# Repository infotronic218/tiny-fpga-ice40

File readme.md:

# Tiny FPGA BOARD DESIGN With KiCad6

# This a simple PFC projec with KiCad 6 based on Lattice ICE40 Serie FPGA 
## The design has 4 layers

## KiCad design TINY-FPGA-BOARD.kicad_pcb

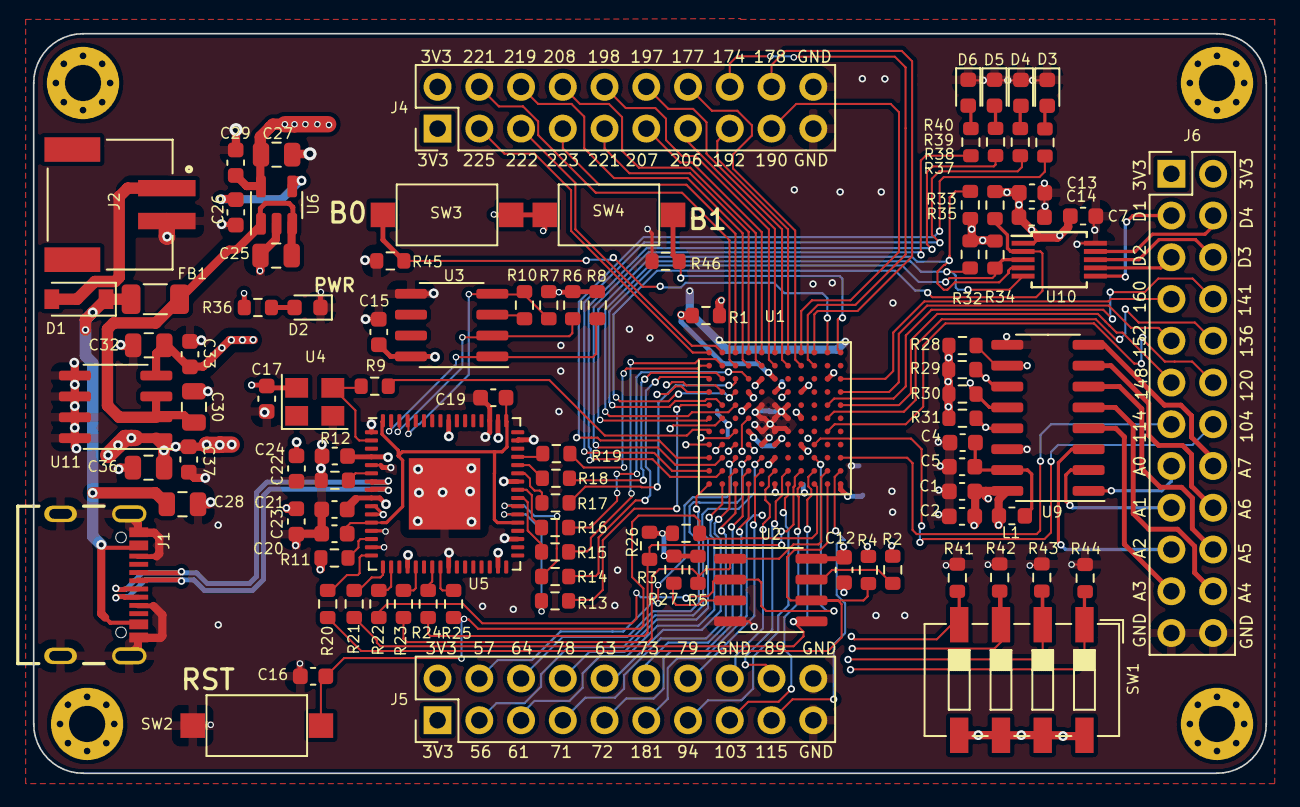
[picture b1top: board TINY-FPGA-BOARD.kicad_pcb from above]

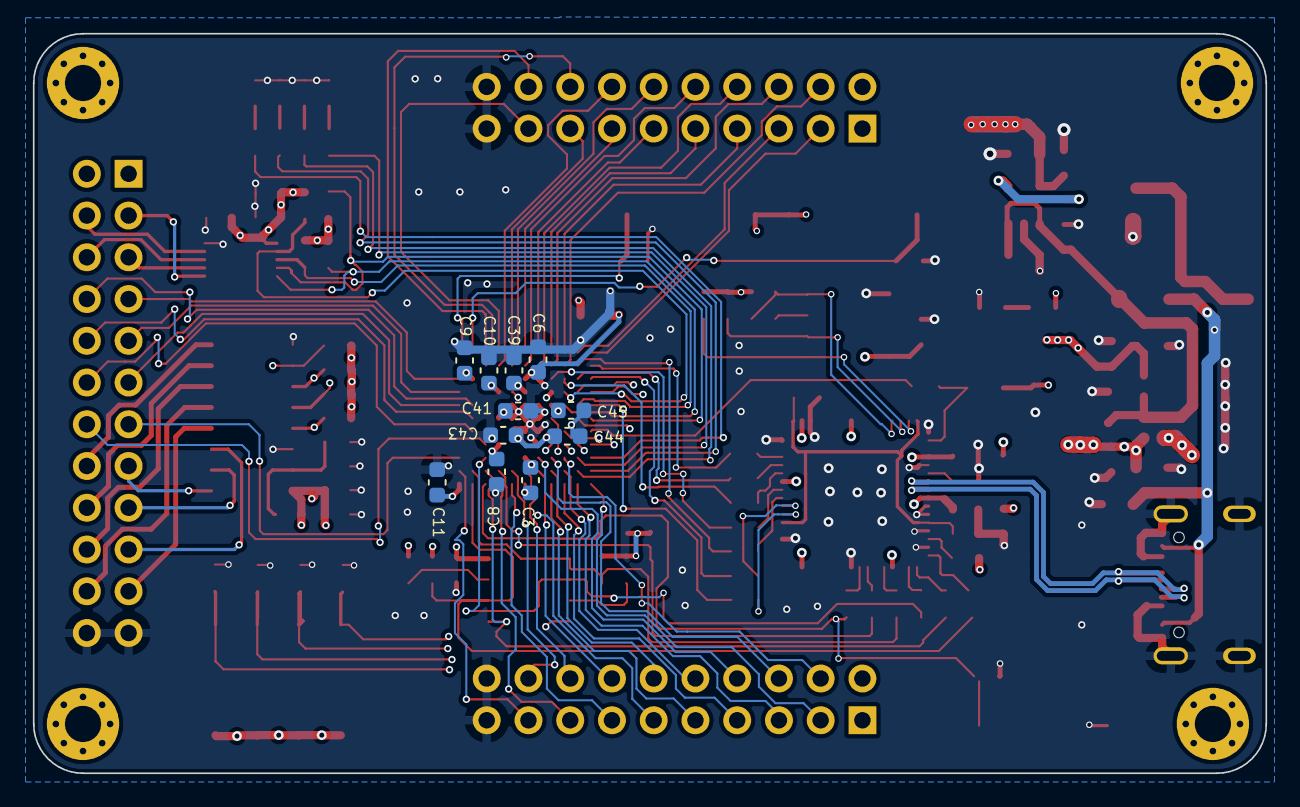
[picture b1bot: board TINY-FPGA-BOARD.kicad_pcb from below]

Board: 4 copper layers, 75.0 x 45.0 mm, 114 parts (11 on the bottom side), 124 nets.

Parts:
C1, C2, C4, C6, C7, C8, C9, C10, C11, C12, C13, C14, C15, C16, C17, C20, C23, C24, C26, C29, C33, C37, C39, C41, C43, C44, C45: 100n; C_0603_1608Metric
C3: 10u; C_0603_1608Metric
C5: 22pF; C_0603_1608Metric
C19, C21, C22: 4.7u; C_0603_1608Metric
C25, C27, C28, C30, C32, C36: 10u; C_0805_2012Metric
D1: D_Schottky; D_SOD-123
D2, D3, D4, D5, D6: LED; LED_0603_1608Metric
FB1: FerriteBead_Small; C_1206_3216Metric
H1, H2, H3, H4: MH; MountingHole_2.2mm_M2_Pad_Via
J1: CON_USB_GCT_USB4105_REVA
J2: DC; JST_S2B-PH-SM4-TB(LF)(SN)
J4, J5: CON; PinHeader_2x10_P2.54mm_Vertical
J6: Conn_02x12_Odd_Even; PinHeader_2x12_P2.54mm_Vertical
L1: 39nH; L_0603_1608Metric
R1: 100R; R_0603_1608Metric
R2, R3, R4, R5, R6, R7, R8, R26, R27, R28, R29, R30, R31, R32, R33, R34, R35, R41, R42, R43, R44, R45, R46: 10K; R_0603_1608Metric
R9, R13, R14, R15, R16, R17, R18, R19, R20, R21, R22, R23, R24, R25: 0R; R_0603_1608Metric
R10, R11: 2.2K; R_0603_1608Metric
R12: 12K; R_0603_1608Metric
R36, R37, R38, R39, R40: 220R; R_0603_1608Metric
SW1: SW_DIP_x04; SW_DIP_SPSTx04_Slide_6.7x11.72mm_W6.73mm_P2.54mm_LowProfile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
SW2, SW3, SW4: RST; SW_SPST_CK_RS282G05A3
U1: ICE40HX8K-BG121; BGA-121_9.0x9.0mm_Layout11x11_P0.8mm_Ball0.4mm_Pad0.35mm_NS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
U2: W25Q128JVS; SOIC-8_3.9x4.9mm_P1.27mm
U3: 93LCxxA; SOIC-8_3.9x4.9mm_P1.27mm
U4: ASDMB-xxxMHz; Crystal_SMD_Abracon_ABM8G-4Pin_3.2x2.5mm
U5: FT2232HQ; QFN-64-1EP_9x9mm_P0.5mm_EP4.35x4.35mm
U6: LDK130-12_SOT23_SOT353; SOT-23-5
U9: MCP3208; SOIC-16_3.9x9.9mm_P1.27mm
U10: MCP4728; MSOP-10_3x3mm_P0.5mm
U11: MIC5212-SJYM; SOIC-8_3.9x4.9mm_P1.27mm

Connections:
+1V2: C8.1, C10.1, C27.1, C29.1, R1.2, U1.D4 (VCC), U1.D8 (VCC), U1.H4 (VCC), U1.H8 (VCC), U6.5 (OUT)
+2V5: C9.1, C32.1, C33.1, U1.C10 (VPP_2V5), U11.4 (OUTB)
+3V3: C1.1, C2.1, C7.1, C11.1, C12.1, C13.1, C14.1, C15.2, C17.1, C21.1, C22.1, C23.1, C24.1, C36.2, C37.2, C39.1, C41.1, C43.1, C44.1, C45.1, J4.1, J4.2, J5.1, J5.2, J6.1, J6.2, L1.1, R2.2, R3.2, R4.2, R5.2, R6.2, R7.2, R8.2, R11.2, R26.2, R27.2, R28.2, R29.2, R30.2, R31.2, R32.2, R33.2, R34.2, R35.2, R36.2, SW1.5, SW1.6, SW1.7, SW1.8, SW3.1, SW4.1, U1.D6 (VCCIO_0), U1.E4 (VCCIO_3), U1.F8 (VCCIO_1), U1.G4 (VCCIO_3), U1.H6 (VCCIO_2), U1.L11 (VCC_SPI), U2.8 (VCC), U3.8 (VCC), U4.4 (VDD), U5.4 (VPHY), U5.9 (VPLL), U5.20 (VCCIO), U5.31 (VCCIO), U5.42 (VCCIO), U5.50 (VREGIN), U5.56 (VCCIO), U9.16 (Vdd), U10.1 (VDD), U11.1 (OUTA)
+5V: C25.1, C30.1, FB1.2, U6.1 (IN), U6.3 (EN), U11.2 (INA), U11.3 (INB)
/CS: R5.1, R23.1, U1.K10 (IOB_108_SS), U2.1 (~CS)
/FPGA IOs BANKS/BTN0: R45.2, SW3.2, U1.A10 (IOT_170)
/FPGA IOs BANKS/BTN1: R46.2, SW4.2, U1.A11 (IOT_168)
/FPGA IOs BANKS/IO56: J5.3, U1.L1 (IOB_56)
/FPGA IOs BANKS/IO57: J5.4, U1.J3 (IOB_57)
/FPGA IOs BANKS/IO61: J5.5, U1.L2 (IOB_61)
/FPGA IOs BANKS/IO63: J5.10, U1.K3 (IOB_63)
/FPGA IOs BANKS/IO64: J5.6, U1.J4 (IOB_64)
/FPGA IOs BANKS/IO71: J5.7, U1.L3 (IOB_71)
/FPGA IOs BANKS/IO72: J5.9, U1.L4 (IOB_72)
/FPGA IOs BANKS/IO73: J5.12, U1.K4 (IOB_73)
/FPGA IOs BANKS/IO78: J5.8, U1.J5 (IOB_78)
/FPGA IOs BANKS/IO79: J5.14, U1.K5 (IOB_79)
/FPGA IOs BANKS/IO82: J5.16, U1.K6 (IOB_82_GBIN4)
/FPGA IOs BANKS/IO89: J5.18, U1.K7 (IOB_89)
/FPGA IOs BANKS/IO94: J5.13, U1.L7 (IOB_94)
/FPGA IOs BANKS/IO103: J5.15, U1.L8 (IOB_103_CBSEL0)
/FPGA IOs BANKS/IO104: J6.14, U1.H9 (IOB_104_CBSEL1)
/FPGA IOs BANKS/IO114: J6.13, U1.J11 (IOR_114)
/FPGA IOs BANKS/IO115: J5.17, U1.K11 (IOR_115)
/FPGA IOs BANKS/IO120: J6.12, U1.G10 (IOR_120)
/FPGA IOs BANKS/IO136: J6.10, U1.F10 (IOR_136)
/FPGA IOs BANKS/IO141: J6.8, U1.E10 (IOR_141_GBIN2)
/FPGA IOs BANKS/IO148: J6.11, U1.E11 (IOR_148)
/FPGA IOs BANKS/IO152: J6.9, U1.D11 (IOR_152)
/FPGA IOs BANKS/IO160: J6.7, U1.C11 (IOR_160)
/FPGA IOs BANKS/IO174: J4.16, U1.B9 (IOT_174)
/FPGA IOs BANKS/IO177: J4.14, U1.B8 (IOT_177)
/FPGA IOs BANKS/IO178: J4.18, U1.A9 (IOT_178)
/FPGA IOs BANKS/IO181: J5.11, U1.D7 (IOT_181)
/FPGA IOs BANKS/IO190: J4.17, U1.A8 (IOT_190)
/FPGA IOs BANKS/IO192: J4.15, U1.A7 (IOT_192)
/FPGA IOs BANKS/IO197: J4.12, U1.B7 (IOT_197_GBIN1)
/FPGA IOs BANKS/IO198: J4.10, U1.B6 (IOT_198_GBIN0)
/FPGA IOs BANKS/IO206: J4.13, U1.A6 (IOT_206)
/FPGA IOs BANKS/IO207: J4.11, U1.A5 (IOT_207)
/FPGA IOs BANKS/IO208: J4.8, U1.B5 (IOT_208)
/FPGA IOs BANKS/IO211: J4.9, U1.A4 (IOT_211)
/FPGA IOs BANKS/IO219: J4.6, U1.B4 (IOT_219)
/FPGA IOs BANKS/IO221: J4.4, U1.B3 (IOT_221)
/FPGA IOs BANKS/IO222: J4.5, U1.A2 (IOT_222)
/FPGA IOs BANKS/IO223: J4.7, U1.A3 (IOT_223)
/FPGA IOs BANKS/IO225: J4.3, U1.A1 (IOT_225)
/FPGA IOs BANKS/LED1: R37.2, U1.J1 (IOL_23A)
/FPGA IOs BANKS/LED2: R38.2, U1.K1 (IOL_23B)
/FPGA IOs BANKS/LED3: R39.2, U1.K2 (IOL_25A)
/FPGA IOs BANKS/LED4: R40.2, U1.J2 (IOL_25B)
/FPGA IOs BANKS/SW1: R44.2, SW1.1, U1.D1 (IOL_8B)
/FPGA IOs BANKS/SW2: R43.2, SW1.2, U1.D2 (IOL_9A)
/FPGA IOs BANKS/SW3: R42.2, SW1.3, U1.F2 (IOL_12B)
/FPGA IOs BANKS/SW4: R41.2, SW1.4, U1.F4 (IOL_13A)
/ICE_CDONE: R24.1, R26.1, U1.K8 (CDONE)
/ICE_CLK: R9.2, U1.G1 (IOL_14A_GBIN6)
/ICE_CREST: C16.1, R25.1, R27.1, SW2.1, U1.L9 (~CRESET)
/MISO: R21.1, U1.K9 (IOB_105_SDO), U2.5 (DI(IO0))
/MOSI: R22.1, U1.J9 (IOB_106_SDI), U2.2 (DO(IO1))
/SCK: R4.1, R20.1, U1.L10 (IOB_107_SCK), U2.6 (CLK)
/USB, SPI, RS232 Interface/FT_DATA: R7.1, R10.1, U3.4 (DO), U5.61 (EEDATA)
/USB, SPI, RS232 Interface/FT_EECLK: R6.1, U3.2 (SCLK), U5.62 (EECLK)
/USB, SPI, RS232 Interface/FT_EECS: R8.1, U3.1 (CS), U5.63 (EECS)
/USB, SPI, RS232 Interface/MISO: R22.2, U5.18 (ADBUS2)
/USB, SPI, RS232 Interface/MOSI: R21.2, U5.17 (ADBUS1)
/USB, SPI, RS232 Interface/SCK: R20.2, U5.16 (ADBUS0)
/USB, SPI, RS232 Interface/SS: R23.2, U5.21 (ADBUS4)
/USB, SPI, RS232 Interface/VCC1_8FT: C19.1, C20.1, U5.12 (VCORE), U5.37 (VCORE), U5.49 (VREGOUT), U5.64 (VCORE)
ADC0: J6.15, U9.1 (CH0)
ADC1: J6.17, U9.2 (CH1)
ADC2: J6.19, U9.3 (CH2)
ADC3: J6.21, U9.4 (CH3)
ADC4: J6.22, U9.5 (CH4)
ADC5: J6.20, U9.6 (CH5)
ADC6: J6.18, U9.7 (CH6)
ADC7: J6.16, U9.8 (CH7)
ADC_DI: R30.1, U1.G3 (IOL_17A), U9.12 (Dout)
ADC_DO: R29.1, U1.H3 (IOL_17B), U9.11 (Din)
ADC_SCLK: R31.1, U1.H2 (IOL_18B), U9.13 (CLK)
ADC_nCS: R28.1, U1.H1 (IOL_18A), U9.10 (~CS/SHDN)
CTSn: R17.1, U1.C3 (IOL_4B)
DAC1: J6.3, U10.6 (VOUTA)
DAC2: J6.5, U10.7 (VOUTB)
DAC3: J6.6, U10.8 (VOUTC)
DAC4: J6.4, U10.9 (VOUTD)
DAC_SCL: R35.1, U1.D3 (IOL_9B), U10.2 (SCL)
DAC_SDA: R34.1, U1.E2 (IOL_10A), U10.3 (SDA)
DAC_nLDAC: R33.1, U1.F1 (IOL_12A), U10.4 (~LDAC)
DAC_nRDY: R32.1, U1.E3 (IOL_10B), U10.5 (RDY/~BSY)
DCDn: R19.1, U1.B1 (IOL_2A)
DSRn: R15.1, U1.B2 (IOL_2B)
DTRn: R16.1, U1.C4 (IOL_4A)
GND: C1.2, C2.2, C3.2, C4.2, C5.2, C6.2, C7.2, C8.2, C9.2, C10.2, C11.2, C12.2, C13.2, C14.2, C15.1, C16.2, C17.2, C19.2, C20.2, C21.2, C22.2, C23.2, C24.2, C25.2, C26.2, C27.2, C28.2, C29.2, C30.2, C32.2, C33.2, C36.1, C37.1, C39.2, C41.2, C43.2, C44.2, C45.2, D2.1 (K), D3.1 (K), D4.1 (K), D5.1 (K), D6.1 (K), J1.A1/B12 (GND), J1.A8 (SBU1), J1.B1/A12 (GND), J1.B8 (SBU2), J1.G1 (GND), J1.G2 (GND), J1.G3 (GND), J1.G4 (GND), J2.2, J4.19, J4.20, J5.19, J5.20, J6.23, J6.24, R12.1, R41.1, R42.1, R43.1, R44.1, R45.1, R46.1, SW2.2, U1.C5 (GNDPLL1), U1.E5 (GND), U1.E6 (GND), U1.E7 (GND), U1.F5 (GND), U1.F6 (GND), U1.F7 (GND), U1.G5 (GND), U1.G6 (GND), U1.G7 (GND), U1.H5 (GND), U1.L6 (GNDPLL0), U2.4 (GND), U3.5 (GND), U4.2 (GND), U5.1 (GND), U5.5 (GND), U5.10 (AGND), U5.11 (GND), U5.13 (TEST), U5.15 (GND), U5.25 (GND), U5.35 (GND), U5.47 (GND), U5.51 (GND), U5.65 (GND), U6.2 (GND), U9.9 (DGND), U9.14 (AGND), U10.10 (VSS), U11.5 (GND), U11.6 (GND), U11.7 (GND), U11.8 (GND)
unnamed: C3.1, C6.1, R1.1, U1.C6 (VCCPLL1), U1.J6 (VCCPLL0)
unnamed: C4.1, C5.1, L1.2, U9.15 (Vref)
unnamed: C26.1, U6.4 (BP)
unnamed: D1.2 (A), J2.1
unnamed: D2.2 (A), R36.1
unnamed: D3.2 (A), R37.1
unnamed: D4.2 (A), R38.1
unnamed: D5.2 (A), R39.1
unnamed: D6.2 (A), R40.1
unnamed: R2.1, U2.7 (IO3)
unnamed: R3.1, U2.3 (IO2)
unnamed: R9.1, U4.3 (Out), U5.2 (OSCI)
unnamed: R10.2, U3.3 (DI)
unnamed: R11.1, U5.14 (~RESET)
unnamed: R12.2, U5.6 (REF)
unnamed: R13.2, U5.38 (BDBUS0)
unnamed: R14.2, U5.39 (BDBUS1)
unnamed: R15.2, U5.40 (BDBUS2)
unnamed: R16.2, U5.41 (BDBUS3)
unnamed: R17.2, U5.43 (BDBUS4)
unnamed: R18.2, U5.44 (BDBUS5)
unnamed: R19.2, U5.45 (BDBUS6)
unnamed: R24.2, U5.23 (ADBUS6)
unnamed: R25.2, U5.24 (ADBUS7)
RS232_RX_TTL: R13.1, U1.E1 (IOL_8A)
RS232_TX_TTL: R14.1, U1.C1 (IOL_5B)
RTSn: R18.1, U1.C2 (IOL_5A)
USB_N: J1.A7 (DN1), J1.B7 (DN2), U5.7 (DM)
USB_P: J1.A6 (DP1), J1.B6 (DP2), U5.8 (DP)
VBUS: C28.1, D1.1 (K), FB1.1, J1.A4/B9 (VBUS), J1.B4/A9 (VBUS)

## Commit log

2022-08-10 First update of the design
2022-08-10 Remove the fab folder
2022-08-10 Update the description
2022-08-10 Update the files
